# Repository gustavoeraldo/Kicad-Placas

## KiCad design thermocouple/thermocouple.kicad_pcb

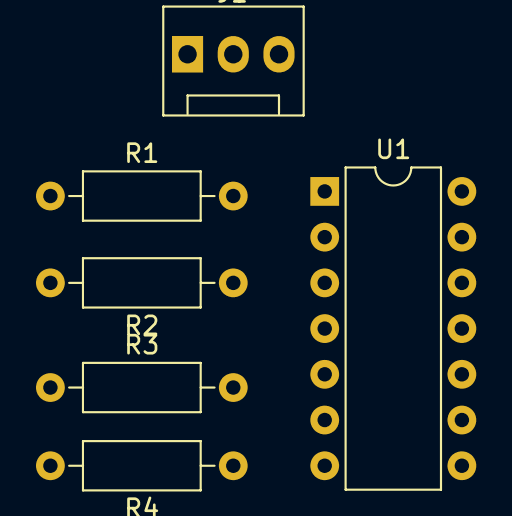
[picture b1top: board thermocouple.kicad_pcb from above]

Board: 2 copper layers, 6 parts (0 on the bottom side), 6 nets, no tracks yet.

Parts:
J1: Conn_01x02; FanPinHeader_1x03_P2.54mm_Vertical
R1, R2, R3, R4: R; R_Axial_DIN0207_L6.3mm_D2.5mm_P10.16mm_Horizontal
U1: LM324A; DIP-14_W7.62mm

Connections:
GND: U1.2, U1.6
unnamed: J1.2, R1.2
unnamed: R1.1, R2.2, U1.3
unnamed: R2.1, R3.2, U1.1
unnamed: R3.1, R4.2, U1.5
unnamed: R4.1, U1.7

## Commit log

2019-10-18 Quase completo
2019-10-18 Placa pronta
